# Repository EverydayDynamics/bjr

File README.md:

# bjr
A Ball Juggling Robot's repository

## Getting started

### firmware build and flashing

install rust on you computer
```
curl --proto '=https' --tlsv1.2 -sSf https://sh.rustup.rs | sh
```
Install the target toolchain

```
rustup target add thumbv7em-none-eabihf
```

Install probe-rs
```
curl --proto '=https' --tlsv1.2 -LsSf https://github.com/probe-rs/probe-rs/releases/latest/download/probe-rs-tools-installer.sh | sh
```
Download and install jlink tools from here
https://www.segger.com/downloads/jlink/
Restart your shell
Change directory to the main software
```
cd software/central_control_firmware
```

Build the firmware with:
```
cargo embed --bin main_app --release 
```
### telemetry visualizer build
Change directory to the visualizer
```
cd software/telemetry_visualizer
```

Build the visualizer with:
```
cargo embed --bin main_app --release 
```

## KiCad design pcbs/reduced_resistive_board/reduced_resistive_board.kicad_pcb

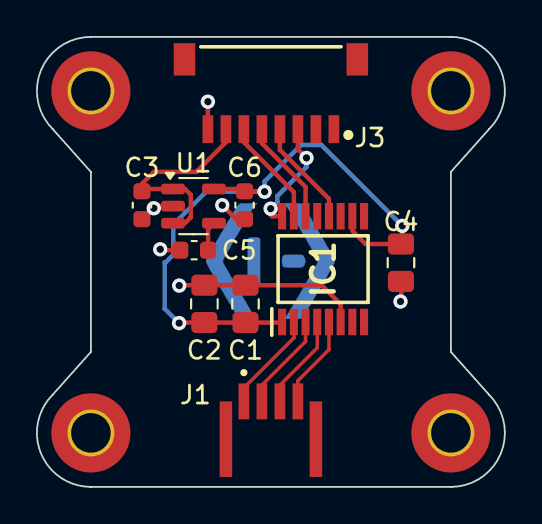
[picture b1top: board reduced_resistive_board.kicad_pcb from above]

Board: 2 copper layers, 26.0 x 25.0 mm, 10 parts (0 on the bottom side), 12 nets.

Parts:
C1, C4: 0.1uF; C_0805_2012Metric_Pad1.18x1.45mm_HandSolder
C2: 10uF; C_0805_2012Metric_Pad1.18x1.45mm_HandSolder
C3, C6: 1uF; C_0603_1608Metric
C5: 0.1uF; C_0603_1608Metric
IC1: TSC2046EIPWR; SOP65P640X120-16N
J1: SFW4R-1STE1HLF; AMPHENOL_SFW4R-1STE1HLF
J3: SM08B-SRSS-TB_LF__SN_; JST_SM08B-SRSS-TB_LF__SN_
U1: SOT-23-5

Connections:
+2V8: C1.1, C2.1, C4.1, C6.1, IC1.1 (+VCC), IC1.10 (IOVDD), U1.5 (V_O)
/CS_TOUCH: IC1.15 (~CS), J3.6
/MISO: IC1.12 (DOUT), J3.4
/MOSI: IC1.14 (DIN), J3.5
/SCK: IC1.16 (DCLK), J3.3
/X+: IC1.2 (X+), J1.1
/X-: IC1.4 (X-), J1.3
/Y+: IC1.3 (Y+), J1.2
/Y-: IC1.5 (Y-), J1.4
GND: C1.2, C2.2, C3.2, C4.2, C5.2, C6.2, IC1.6 (GND), J3.8, U1.2 (GND)
unnamed: C5.1, U1.4 (BYPASS)
VDD: C3.1, J3.7, U1.1 (V_I), U1.3 (V_INH)

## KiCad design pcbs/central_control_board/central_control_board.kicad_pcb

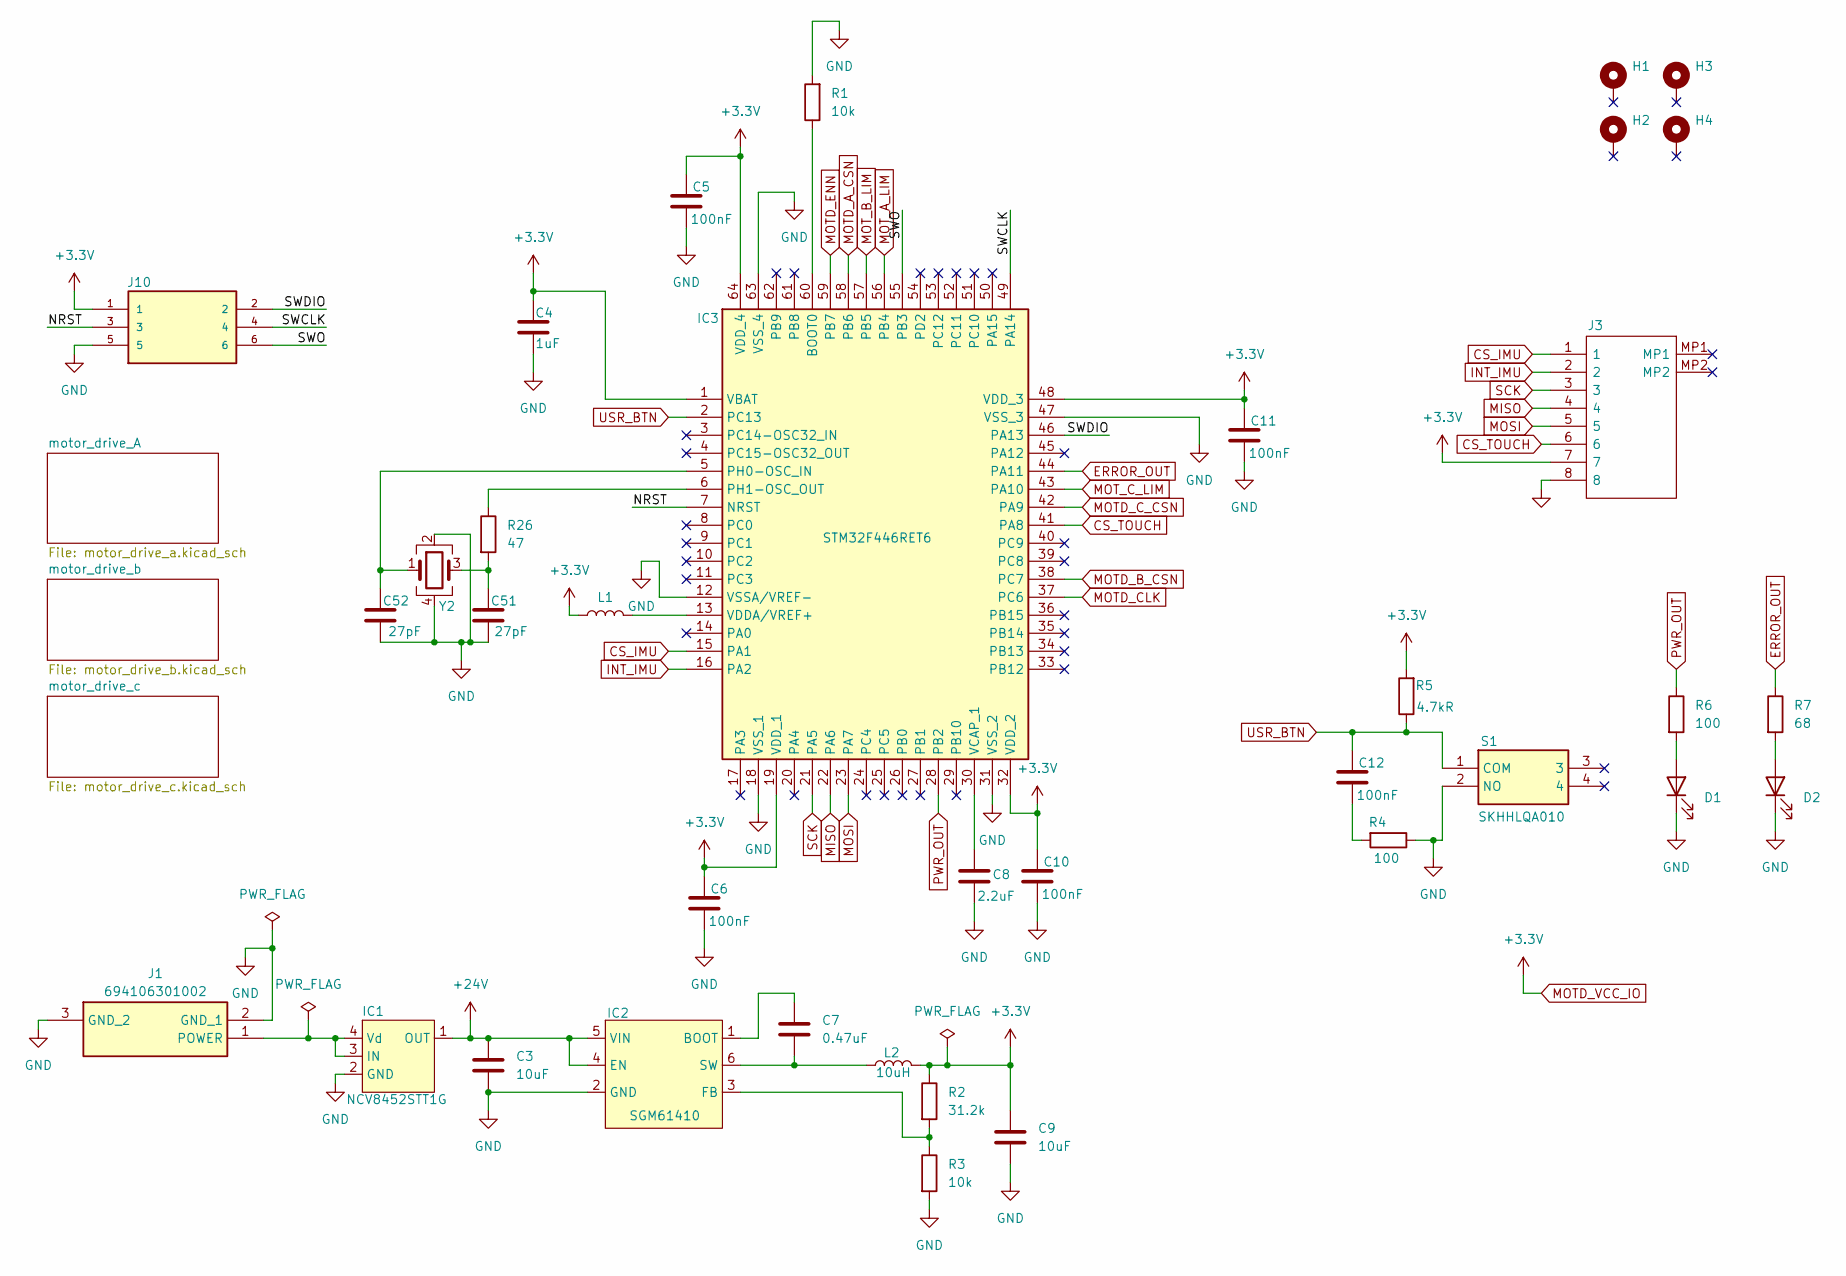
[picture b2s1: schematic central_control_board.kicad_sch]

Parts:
C3, C9: 10uF; C_1206_3216Metric_Pad1.33x1.80mm_HandSolder
C4: 1uF; C_0603_1608Metric_Pad1.08x0.95mm_HandSolder
C5, C6, C10, C11, C12: 100nF; C_0603_1608Metric_Pad1.08x0.95mm_HandSolder
C7: 0.47uF; C_0603_1608Metric_Pad1.08x0.95mm_HandSolder
C8: 2.2uF; C_0603_1608Metric_Pad1.08x0.95mm_HandSolder
C51, C52: 27pF; C_0603_1608Metric_Pad1.08x0.95mm_HandSolder
D1: LED red; LED_0603_1608Metric_Pad1.05x0.95mm_HandSolder
D2: LED white; LED_0603_1608Metric_Pad1.05x0.95mm_HandSolder
H1, H2, H3, H4: MountingHole_Pad; MountingHole_2.7mm_M2.5_ISO14580_Pad
IC1: NCV8452STT1G; SOT-223
IC2: SGM61410; SOT-23-6; mfg_part_num SGM61410XN6G/TR
IC3: STM32F446RET6; LQFP64-10x10mm; Manufacturer_Part_Number STM32F446RET6
J1: 694106301002; Manufacturer_Part_Number 694106301002
J3: BM08B-SRSS-TBT_LF__SN_; BM08BSRSSTBTLFSN; Manufacturer_Part_Number BM08B-SRSS-TBT(LF)(SN)
J10: 8.06.16_J-LINK_6-PIN_NEEDLE_ADAPTER; SEGGER_8.06.16_J-LINK_6-PIN_NEEDLE_ADAPTER; PARTREV A
L1: bead; L_1206_3216Metric
L2: 10uH; LQH3NPN100MJRL
R1, R3: 10k; R_0603_1608Metric_Pad0.98x0.95mm_HandSolder
R2: 31.2k; R_0603_1608Metric_Pad0.98x0.95mm_HandSolder
R4, R6: 100; R_0603_1608Metric_Pad0.98x0.95mm_HandSolder
R5: 4.7kR; R_0603_1608Metric_Pad0.98x0.95mm_HandSolder
R7: 68; R_0603_1608Metric_Pad0.98x0.95mm_HandSolder
R26: 47; R_0603_1608Metric_Pad0.98x0.95mm_HandSolder
S1: SKHHLQA010
Y2: Crystal_GND24; Crystal_SMD_5032-4Pin_5.0x3.2mm

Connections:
+24V: C3.1, IC1.1 (OUT), IC2.4 (EN), IC2.5 (VIN); also elsewhere on the board
/NRST: IC3.7 (NRST), J10.3
/SWCLK: IC3.49 (PA14), J10.4
/SWDIO: IC3.46 (PA13), J10.2
/SWO: IC3.55 (PB3), J10.6
CS_IMU: IC3.15 (PA1), J3.1
CS_TOUCH: IC3.41 (PA8), J3.6
ERROR_OUT: IC3.44 (PA11), R7.1
GND: C3.2, C4.1, C5.2, C6.2, C8.1, C9.2, C10.2, C11.2, C51.2, C52.2, D1.1 (K), D2.1 (K), IC1.2 (GND), IC2.2 (GND), IC3.12 (VSSA/VREF-), IC3.18 (VSS_1), IC3.31 (VSS_2), IC3.47 (VSS_3), IC3.63 (VSS_4), J1.2 (GND_1), J1.3 (GND_2), J3.8, J10.5, R1.2, R3.2, R4.1, S1.2 (NO), Y2.2, Y2.4; also elsewhere on the board
INT_IMU: IC3.16 (PA2), J3.2
MISO: IC3.22 (PA6), J3.4; also elsewhere on the board
MOSI: IC3.23 (PA7), J3.5; also elsewhere on the board
MOTD_A_CSN: IC3.58 (PB6); also elsewhere on the board
MOTD_B_CSN: IC3.38 (PC7); also elsewhere on the board
MOTD_CLK: IC3.37 (PC6); also elsewhere on the board
MOTD_C_CSN: IC3.42 (PA9); also elsewhere on the board
MOTD_ENN: IC3.59 (PB7); also elsewhere on the board
MOTD_VCC_IO: C4.2, C5.1, C6.1, C9.1, C10.1, C11.1, IC3.1 (VBAT), IC3.19 (VDD_1), IC3.32 (VDD_2), IC3.48 (VDD_3), IC3.64 (VDD_4), J3.7, J10.1, L1.1, L2.2, R2.1, R5.2; also elsewhere on the board
MOT_A_LIM: IC3.56 (PB4); also elsewhere on the board
MOT_B_LIM: IC3.57 (PB5); also elsewhere on the board
MOT_C_LIM: IC3.43 (PA10); also elsewhere on the board
unnamed: C12.2, R4.2
unnamed: C51.1, R26.2, Y2.3
unnamed: D1.2 (A), R6.2
unnamed: D2.2 (A), R7.2
unnamed: IC1.3 (IN), IC1.4 (Vd), J1.1 (POWER)
unnamed: C7.1, IC2.1 (BOOT)
unnamed: IC2.3 (FB), R2.2, R3.1
unnamed: C7.2, IC2.6 (SW), L2.1
unnamed: IC3.60 (BOOT0), R1.1
unnamed: C52.1, IC3.5 (PH0-OSC_IN), Y2.1
unnamed: IC3.6 (PH1-OSC_OUT), R26.1
unnamed: C8.2, IC3.30 (VCAP_1)
unnamed: IC3.13 (VDDA/VREF+), L1.2
PWR_OUT: IC3.28 (PB2), R6.1
SCK: IC3.21 (PA5), J3.3; also elsewhere on the board
USR_BTN: C12.1, IC3.2 (PC13), R5.1, S1.1 (COM)

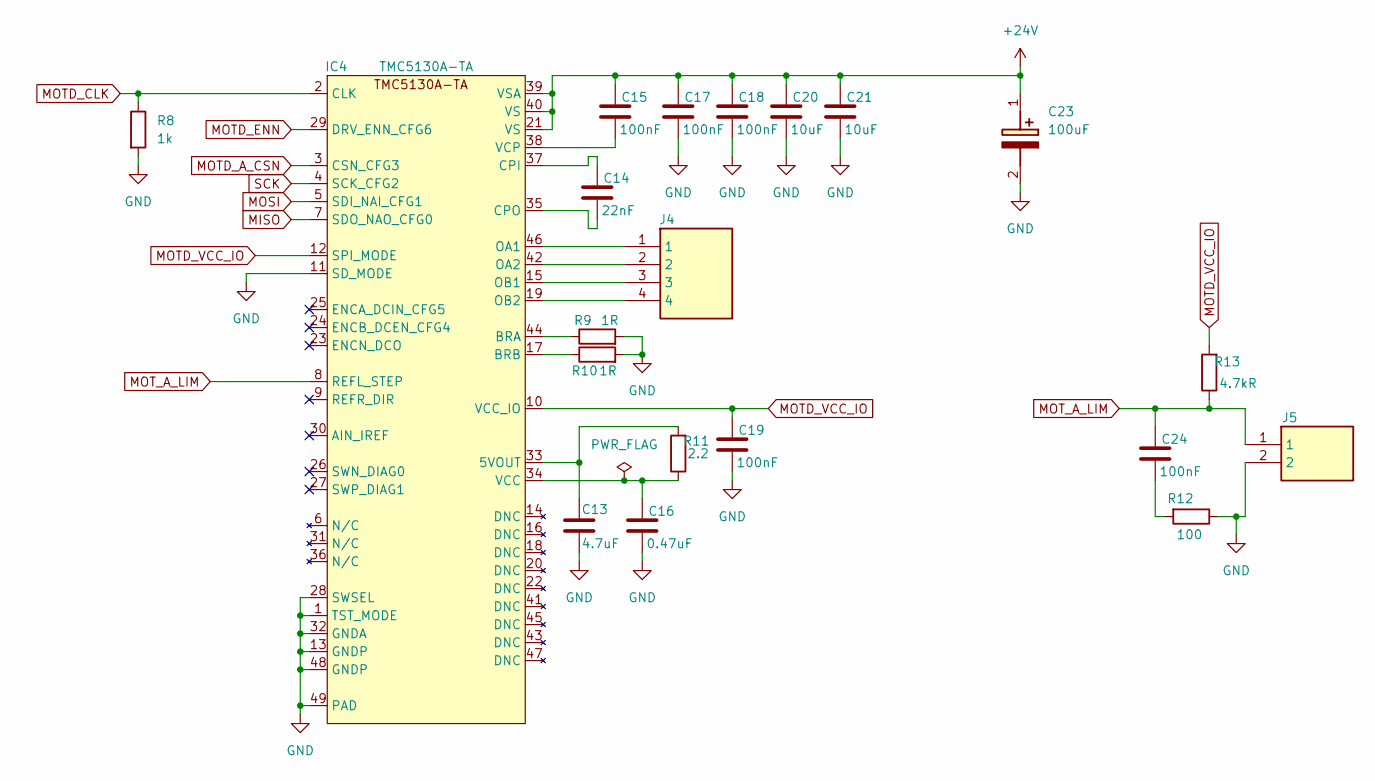
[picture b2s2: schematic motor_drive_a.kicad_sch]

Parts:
C13: 4.7uF; C_0603_1608Metric_Pad1.08x0.95mm_HandSolder
C14: 22nF; C_0603_1608Metric_Pad1.08x0.95mm_HandSolder
C15, C17, C18, C19, C24: 100nF; C_0603_1608Metric_Pad1.08x0.95mm_HandSolder
C16: 0.47uF; C_0603_1608Metric_Pad1.08x0.95mm_HandSolder
C20, C21: 10uF; C_1206_3216Metric_Pad1.33x1.80mm_HandSolder
C23: 100uF; CAPPRD250W50D655H1250
IC4: TMC5130A-TA; TQFP-48-1EP_7x7mm_P0.5mm_EP5x5mm_ThermalVias
J4: B4B-ZR_LF__SN_; SHDR4W50P0X150_1X4_750X350X450P; Manufacturer_Part_Number B4B-ZR(LF)(SN)
J5: B2B-ZR_LF__SN_; SHDR2W50P0X150_1X2_450X350X450P; Manufacturer_Part_Number B2B-ZR(LF)(SN)
R8: 1k; R_0603_1608Metric_Pad0.98x0.95mm_HandSolder
R9, R10: 1R; R_1206_3216Metric_Pad1.30x1.75mm_HandSolder
R11: 2.2; R_0603_1608Metric_Pad0.98x0.95mm_HandSolder
R12: 100; R_0603_1608Metric_Pad0.98x0.95mm_HandSolder
R13: 4.7kR; R_0603_1608Metric_Pad0.98x0.95mm_HandSolder

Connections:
+24V: C15.1, C17.1, C18.1, C20.1, C21.1, C23.1 (+), IC4.21 (VS), IC4.39 (VSA), IC4.40 (VS); also elsewhere on the board
GND: C13.2, C16.2, C17.2, C18.2, C19.2, C20.2, C21.2, C23.2 (-), IC4.1 (TST_MODE), IC4.11 (SD_MODE), IC4.13 (GNDP), IC4.28 (SWSEL), IC4.32 (GNDA), IC4.48 (GNDP), IC4.49 (PAD), J5.2, R8.2, R9.2, R10.2, R12.1; also elsewhere on the board
MISO: IC4.7 (SDO_NAO_CFG0); also elsewhere on the board
MOSI: IC4.5 (SDI_NAI_CFG1); also elsewhere on the board
MOTD_A_CSN: IC4.3 (CSN_CFG3); also elsewhere on the board
MOTD_CLK: IC4.2 (CLK), R8.1; also elsewhere on the board
MOTD_ENN: IC4.29 (DRV_ENN_CFG6); also elsewhere on the board
MOTD_VCC_IO: C19.1, IC4.10 (VCC_IO), IC4.12 (SPI_MODE), R13.2; also elsewhere on the board
MOT_A_LIM: C24.1, IC4.8 (REFL_STEP), J5.1, R13.1; also elsewhere on the board
unnamed: C24.2, R12.2
unnamed: C13.1, IC4.33 (5VOUT), R11.2
unnamed: IC4.44 (BRA), R9.1
unnamed: IC4.17 (BRB), R10.1
unnamed: C14.1, IC4.37 (CPI)
unnamed: C14.2, IC4.35 (CPO)
unnamed: IC4.46 (OA1), J4.1
unnamed: IC4.42 (OA2), J4.2
unnamed: IC4.15 (OB1), J4.3
unnamed: IC4.19 (OB2), J4.4
unnamed: C16.1, IC4.34 (VCC), R11.1
unnamed: C15.2, IC4.38 (VCP)
SCK: IC4.4 (SCK_CFG2); also elsewhere on the board

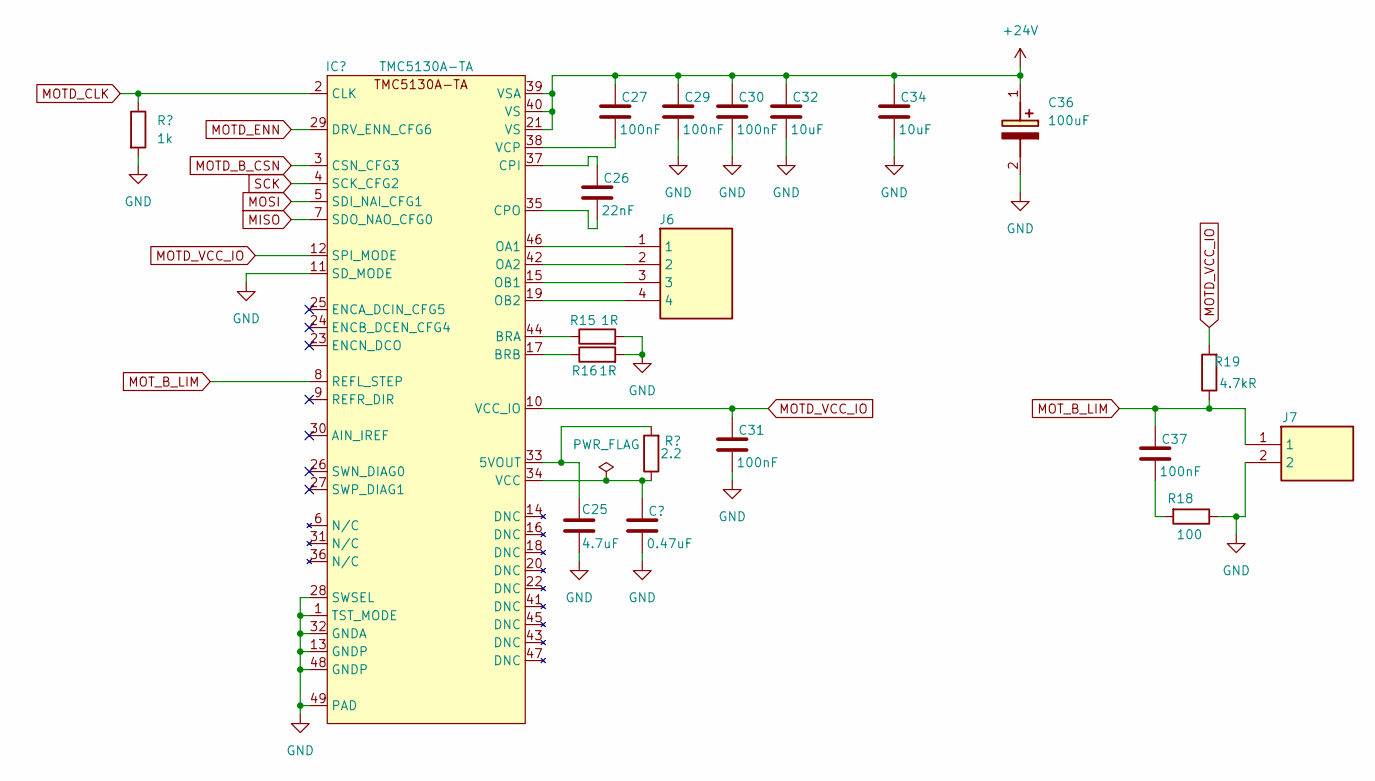
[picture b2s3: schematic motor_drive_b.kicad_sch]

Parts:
C25: 4.7uF; C_0603_1608Metric_Pad1.08x0.95mm_HandSolder
C26: 22nF; C_0603_1608Metric_Pad1.08x0.95mm_HandSolder
C27, C29, C30, C31, C37: 100nF; C_0603_1608Metric_Pad1.08x0.95mm_HandSolder
C28: 0.47uF; C_0603_1608Metric_Pad1.08x0.95mm_HandSolder
C32, C34: 10uF; C_1206_3216Metric_Pad1.33x1.80mm_HandSolder
C36: 100uF; CAPPRD250W50D655H1250
IC5: TMC5130A-TA; TQFP-48-1EP_7x7mm_P0.5mm_EP5x5mm_ThermalVias
J6: B4B-ZR_LF__SN_; SHDR4W50P0X150_1X4_750X350X450P; Manufacturer_Part_Number B4B-ZR(LF)(SN)
J7: B2B-ZR_LF__SN_; SHDR2W50P0X150_1X2_450X350X450P; Manufacturer_Part_Number B2B-ZR(LF)(SN)
R14: 1k; R_0603_1608Metric_Pad0.98x0.95mm_HandSolder
R15, R16: 1R; R_1206_3216Metric_Pad1.30x1.75mm_HandSolder
R17: 2.2; R_0603_1608Metric_Pad0.98x0.95mm_HandSolder
R18: 100; R_0603_1608Metric_Pad0.98x0.95mm_HandSolder
R19: 4.7kR; R_0603_1608Metric_Pad0.98x0.95mm_HandSolder

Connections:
+24V: C27.1, C29.1, C30.1, C32.1, C34.1, C36.1 (+), IC5.21 (VS), IC5.39 (VSA), IC5.40 (VS); also elsewhere on the board
GND: C25.2, C28.2, C29.2, C30.2, C31.2, C32.2, C34.2, C36.2 (-), IC5.1 (TST_MODE), IC5.11 (SD_MODE), IC5.13 (GNDP), IC5.28 (SWSEL), IC5.32 (GNDA), IC5.48 (GNDP), IC5.49 (PAD), J7.2, R14.2, R15.2, R16.2, R18.1; also elsewhere on the board
MISO: IC5.7 (SDO_NAO_CFG0); also elsewhere on the board
MOSI: IC5.5 (SDI_NAI_CFG1); also elsewhere on the board
MOTD_B_CSN: IC5.3 (CSN_CFG3); also elsewhere on the board
MOTD_CLK: IC5.2 (CLK), R14.1; also elsewhere on the board
MOTD_ENN: IC5.29 (DRV_ENN_CFG6); also elsewhere on the board
MOTD_VCC_IO: C31.1, IC5.10 (VCC_IO), IC5.12 (SPI_MODE), R19.2; also elsewhere on the board
MOT_B_LIM: C37.1, IC5.8 (REFL_STEP), J7.1, R19.1; also elsewhere on the board
unnamed: C37.2, R18.2
unnamed: C25.1, IC5.33 (5VOUT), R17.2
unnamed: IC5.44 (BRA), R15.1
unnamed: IC5.17 (BRB), R16.1
unnamed: C26.1, IC5.37 (CPI)
unnamed: C26.2, IC5.35 (CPO)
unnamed: IC5.46 (OA1), J6.1
unnamed: IC5.42 (OA2), J6.2
unnamed: IC5.15 (OB1), J6.3
unnamed: IC5.19 (OB2), J6.4
unnamed: C28.1, IC5.34 (VCC), R17.1
unnamed: C27.2, IC5.38 (VCP)
SCK: IC5.4 (SCK_CFG2); also elsewhere on the board

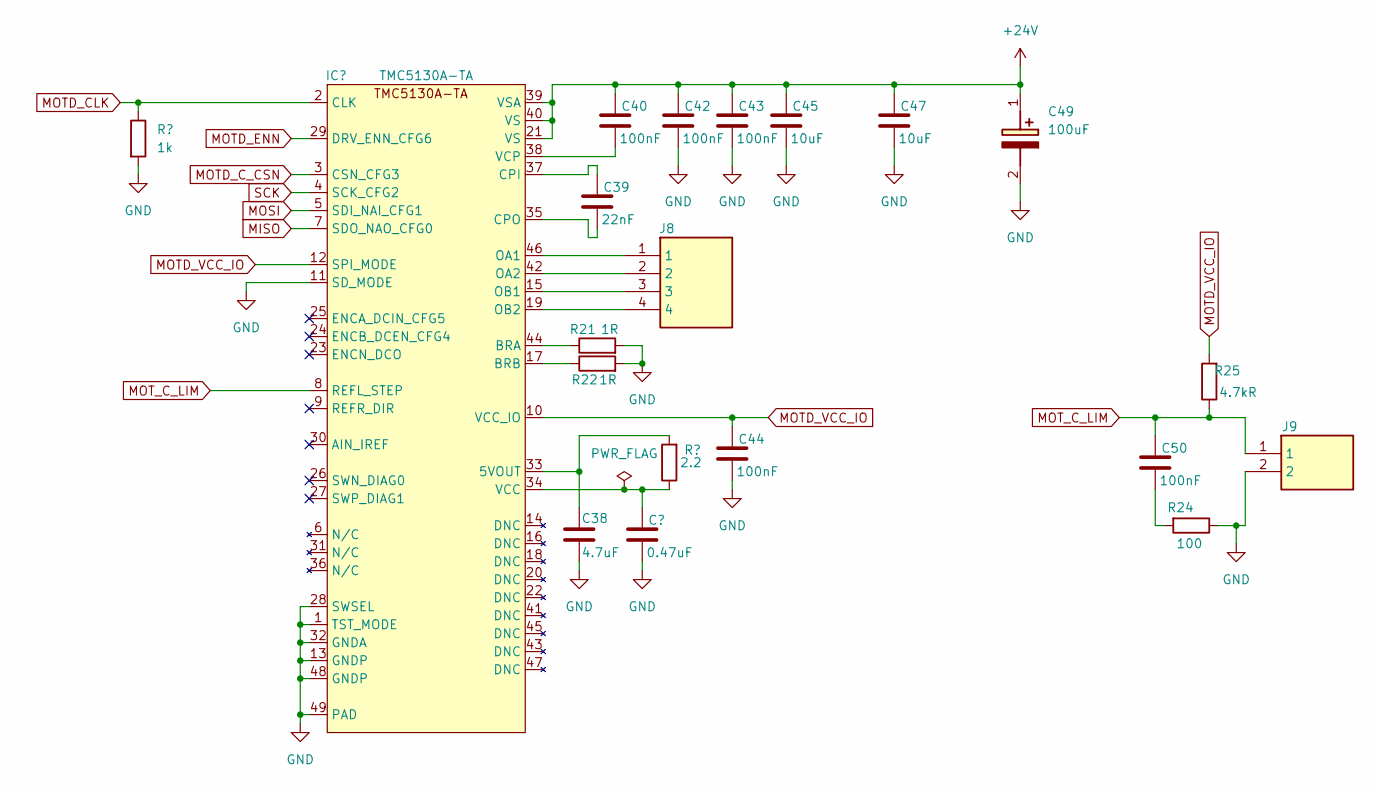
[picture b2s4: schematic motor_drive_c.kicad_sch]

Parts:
C38: 4.7uF; C_0603_1608Metric_Pad1.08x0.95mm_HandSolder
C39: 22nF; C_0603_1608Metric_Pad1.08x0.95mm_HandSolder
C40, C42, C43, C44, C50: 100nF; C_0603_1608Metric_Pad1.08x0.95mm_HandSolder
C41: 0.47uF; C_0603_1608Metric_Pad1.08x0.95mm_HandSolder
C45, C47: 10uF; C_1206_3216Metric_Pad1.33x1.80mm_HandSolder
C49: 100uF; CAPPRD250W50D655H1250
IC6: TMC5130A-TA; TQFP-48-1EP_7x7mm_P0.5mm_EP5x5mm_ThermalVias
J8: B4B-ZR_LF__SN_; SHDR4W50P0X150_1X4_750X350X450P; Manufacturer_Part_Number B4B-ZR(LF)(SN)
J9: B2B-ZR_LF__SN_; SHDR2W50P0X150_1X2_450X350X450P; Manufacturer_Part_Number B2B-ZR(LF)(SN)
R20: 1k; R_0603_1608Metric_Pad0.98x0.95mm_HandSolder
R21, R22: 1R; R_1206_3216Metric_Pad1.30x1.75mm_HandSolder
R23: 2.2; R_0603_1608Metric_Pad0.98x0.95mm_HandSolder
R24: 100; R_0603_1608Metric_Pad0.98x0.95mm_HandSolder
R25: 4.7kR; R_0603_1608Metric_Pad0.98x0.95mm_HandSolder

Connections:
+24V: C40.1, C42.1, C43.1, C45.1, C47.1, C49.1 (+), IC6.21 (VS), IC6.39 (VSA), IC6.40 (VS); also elsewhere on the board
GND: C38.2, C41.2, C42.2, C43.2, C44.2, C45.2, C47.2, C49.2 (-), IC6.1 (TST_MODE), IC6.11 (SD_MODE), IC6.13 (GNDP), IC6.28 (SWSEL), IC6.32 (GNDA), IC6.48 (GNDP), IC6.49 (PAD), J9.2, R20.2, R21.2, R22.2, R24.1; also elsewhere on the board
MISO: IC6.7 (SDO_NAO_CFG0); also elsewhere on the board
MOSI: IC6.5 (SDI_NAI_CFG1); also elsewhere on the board
MOTD_CLK: IC6.2 (CLK), R20.1; also elsewhere on the board
MOTD_C_CSN: IC6.3 (CSN_CFG3); also elsewhere on the board
MOTD_ENN: IC6.29 (DRV_ENN_CFG6); also elsewhere on the board
MOTD_VCC_IO: C44.1, IC6.10 (VCC_IO), IC6.12 (SPI_MODE), R25.2; also elsewhere on the board
MOT_C_LIM: C50.1, IC6.8 (REFL_STEP), J9.1, R25.1; also elsewhere on the board
unnamed: C50.2, R24.2
unnamed: C38.1, IC6.33 (5VOUT), R23.2
unnamed: IC6.44 (BRA), R21.1
unnamed: IC6.17 (BRB), R22.1
unnamed: C39.1, IC6.37 (CPI)
unnamed: C39.2, IC6.35 (CPO)
unnamed: IC6.46 (OA1), J8.1
unnamed: IC6.42 (OA2), J8.2
unnamed: IC6.15 (OB1), J8.3
unnamed: IC6.19 (OB2), J8.4
unnamed: C41.1, IC6.34 (VCC), R23.1
unnamed: C40.2, IC6.38 (VCP)
SCK: IC6.4 (SCK_CFG2); also elsewhere on the board

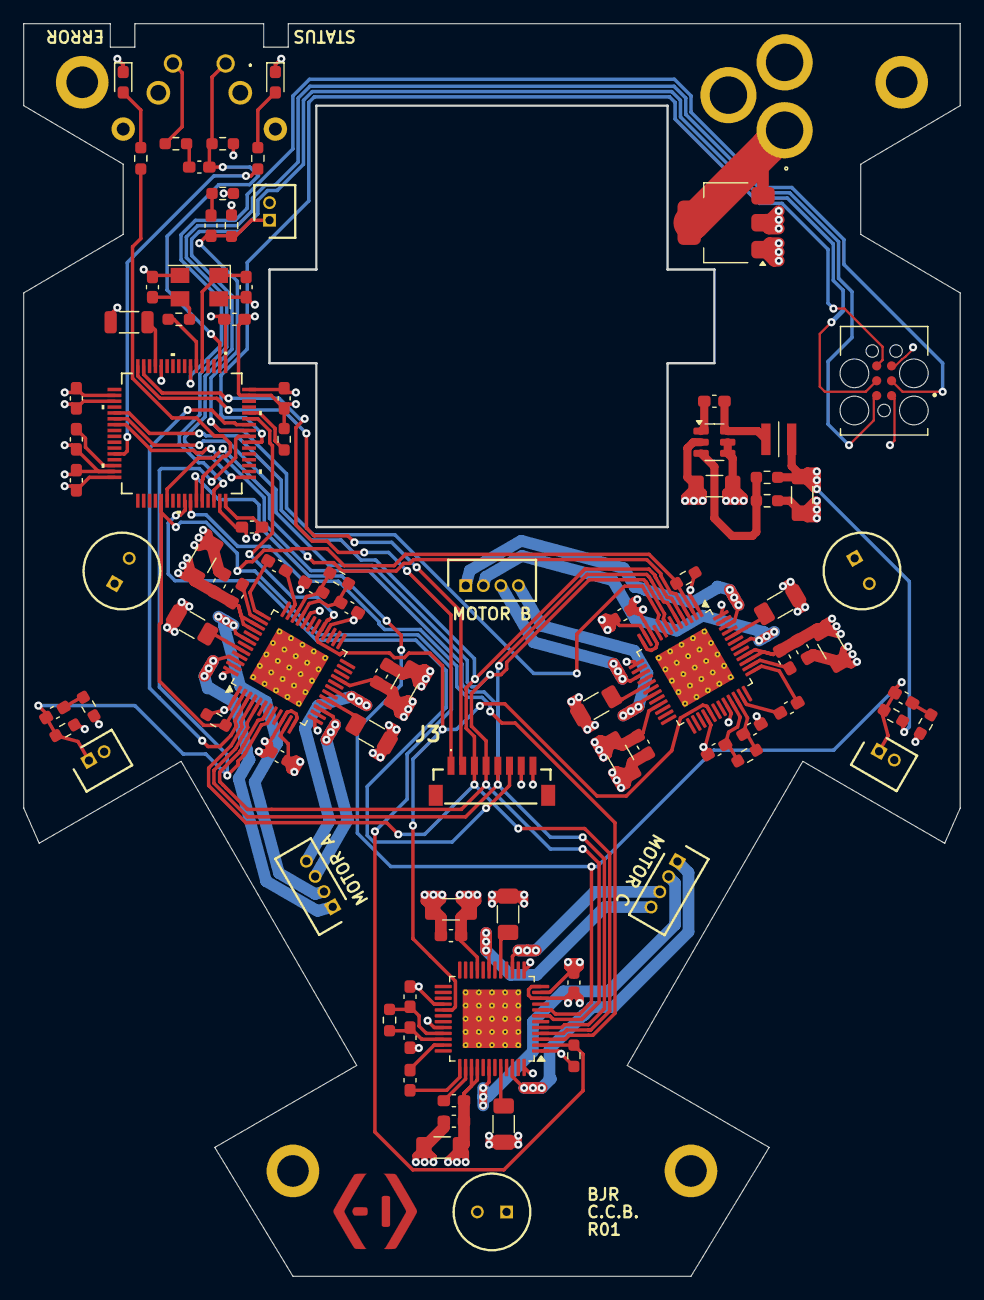
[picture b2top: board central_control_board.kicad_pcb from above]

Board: 4 copper layers, 80.0 x 107.0 mm, 96 parts (0 on the bottom side), 73 nets.

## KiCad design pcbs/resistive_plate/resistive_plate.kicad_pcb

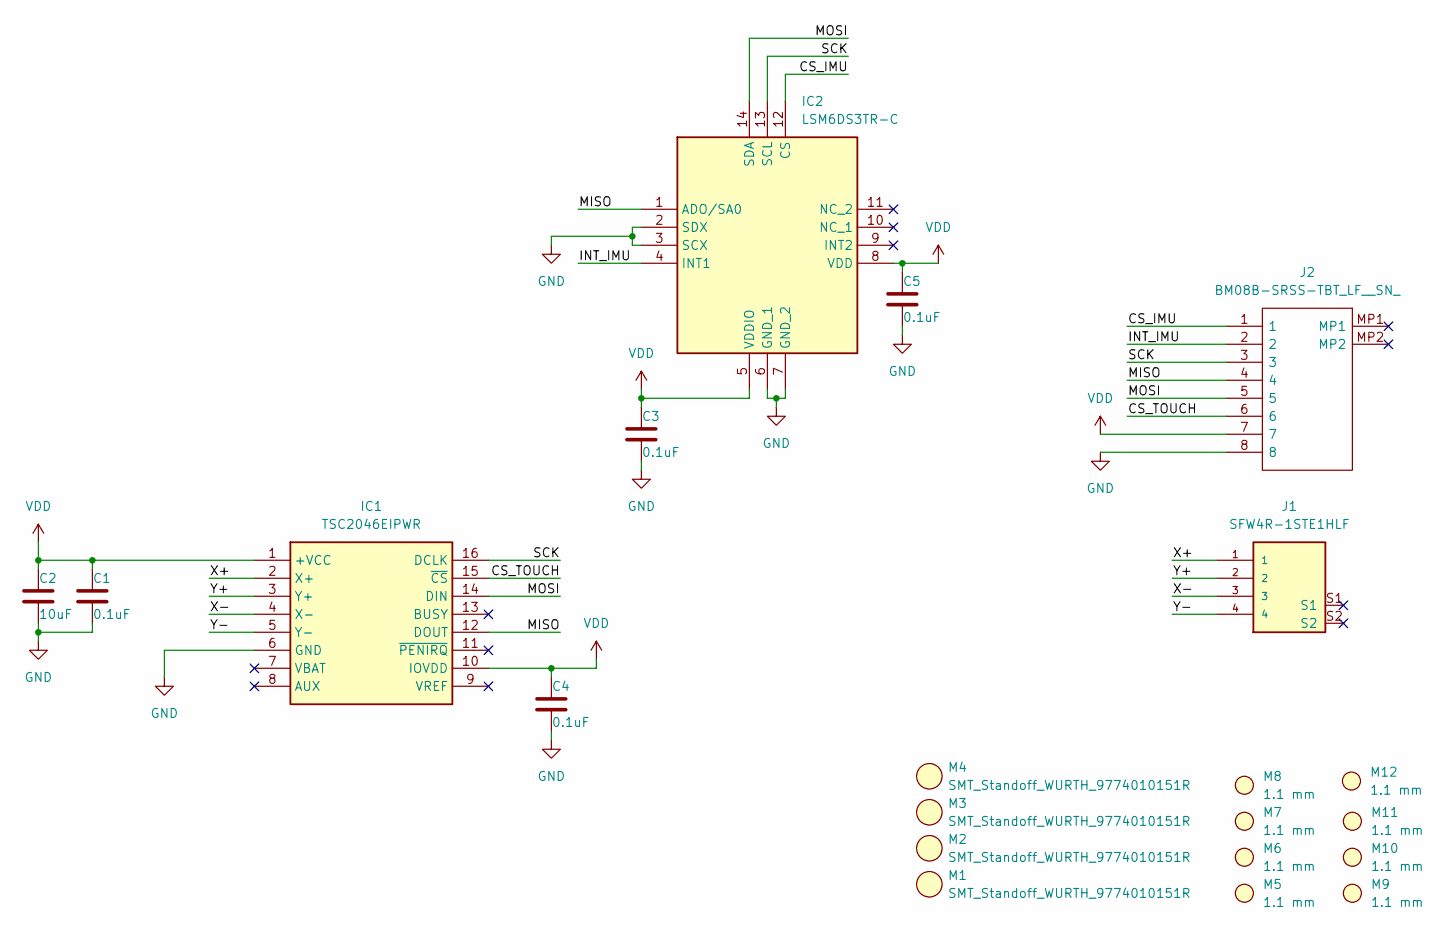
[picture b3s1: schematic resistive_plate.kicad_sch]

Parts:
C1, C3, C4, C5: 0.1uF; C_0805_2012Metric_Pad1.18x1.45mm_HandSolder
C2: 10uF; C_0805_2012Metric_Pad1.18x1.45mm_HandSolder
IC1: TSC2046EIPWR; SOP65P640X120-16N; Mouser Part Number 595-TSC2046EIPWR
IC2: LSM6DS3TR-C; LGA-14_2.5X3X0.86_; Mouser Part Number 511-LSM6DS3TR-C
J1: SFW4R-1STE1HLF; AMPHENOL_SFW4R-1STE1HLF; PARTREV B
J2: BM08B-SRSS-TBT_LF__SN_; BM08BSRSSTBTLFSN; Manufacturer_Part_Number BM08B-SRSS-TBT(LF)(SN)
M1, M2, M3, M4: WURTH ELEKTRONIK 9774010151R
M5, M6, M7, M8, M9, M10, M11, M12: 1.1 mm; Mounting hole 1.1 mm

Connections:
/CS_IMU: IC2.12 (CS), J2.1
/CS_TOUCH: IC1.15 (~CS), J2.6
/INT_IMU: IC2.4 (INT1), J2.2
/MISO: IC1.12 (DOUT), IC2.1 (ADO/SA0), J2.4
/MOSI: IC1.14 (DIN), IC2.14 (SDA), J2.5
/SCK: IC1.16 (DCLK), IC2.13 (SCL), J2.3
/X+: IC1.2 (X+), J1.1
/X-: IC1.4 (X-), J1.3
/Y+: IC1.3 (Y+), J1.2
/Y-: IC1.5 (Y-), J1.4
GND: C1.2, C2.2, C3.2, C4.2, C5.2, IC1.6 (GND), IC2.2 (SDX), IC2.3 (SCX), IC2.6 (GND_1), IC2.7 (GND_2), J2.8
VDD: C1.1, C2.1, C3.1, C4.1, C5.1, IC1.1 (+VCC), IC1.10 (IOVDD), IC2.5 (VDDIO), IC2.8 (VDD), J2.7

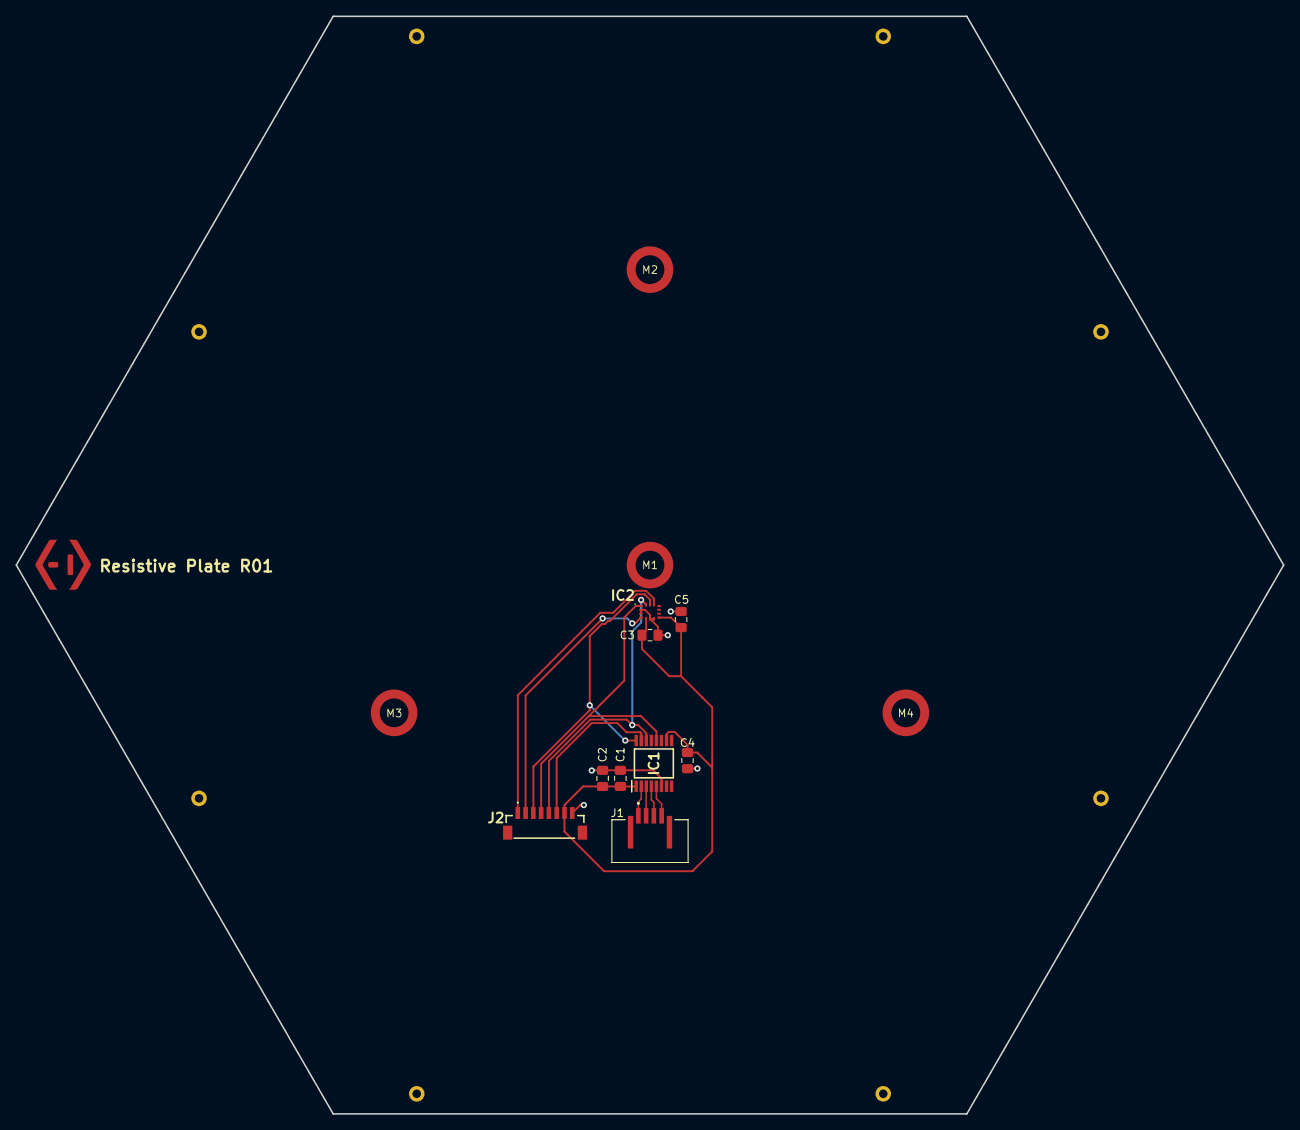
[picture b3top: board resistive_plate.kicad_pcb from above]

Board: 2 copper layers, 163.0 x 141.2 mm, 21 parts (0 on the bottom side), 12 nets.

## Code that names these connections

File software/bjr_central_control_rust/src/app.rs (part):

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    use core::sync::atomic::Ordering;
    use stm32f4xx_hal::{timer::{CounterUs, Event},
                        gpio::{gpioa::PA0,
                               gpioa::PA5,
                               gpioa::PA1,
                               gpioa::PA4,
                               gpioa::PA6,
                               gpioa::PA7,
                               gpioa::PA8,
                               gpioa::PA9,
                               gpiob::PB4,
                               gpiob::PB5,
                               gpiob::PB6,
                               Output, Input},
                        i2c::I2c,
                        pac::I2C1,
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    const SYSFREQ: u32 = 150_000_000;
    static STEPPERS_STATE: [StepperState;NUM_ACTUATOR] = [StepperState::new(),StepperState::new(),StepperState::new()];
    type MotorLiteral= MotorEnum<
        LinearStepperMotor<'static, Lga201s06AUecb019, SilentStepStick<PB4<Input>>>,
        LinearStepperMotor<'static, Lga201s06AUecb019, SilentStepStick<PB5<Input>>>,
        LinearStepperMotor<'static, Lga201s06AUecb019, SilentStepStick<PB6<Input>>>
    >;
    // Shared resources go here
    #[shared]
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        i2c: Option<I2c<I2C1>>,
        controller_task: ControllerTask,
        initializer_task: Initializer,
        stepper_task_a: StepperCtrlrTask<'static, PA5<Output>,PA0<Output>>,
        stepper_task_b: StepperCtrlrTask<'static, PA6<Output>,PA7<Output>>,
        stepper_task_c: StepperCtrlrTask<'static, PA8<Output>,PA9<Output>>,
        stepper_main_timer: CounterUs<stm32f4xx_hal::pac::TIM2>,
        time: u64,
        debug_pin: PA1<Output>,
        debug_pin2: PA4<Output>,
    }
    #[monotonic(binds = TIM3, default = true)]
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        let gpiob = ctx.device.GPIOB.split();
        // button
        // led
        let stepper_a_stp_pin = gpioa.pa5.into_push_pull_output();
        let stepper_a_dir_pin = gpioa.pa0.into_push_pull_output();
        let stepper_a_diag_pin = gpiob.pb4.into_pull_down_input();

        let stepper_b_stp_pin = gpioa.pa6.into_push_pull_output();
        let stepper_b_dir_pin = gpioa.pa7.into_push_pull_output();
        let stepper_b_diag_pin = gpiob.pb5.into_pull_down_input();

        let stepper_c_stp_pin = gpioa.pa8.into_push_pull_output();
        let stepper_c_dir_pin = gpioa.pa9.into_push_pull_output();
        let stepper_c_diag_pin = gpiob.pb6.into_pull_down_input();

        let mut debug_pin = gpioa.pa1.into_push_pull_output();
        let mut debug_pin2 = gpioa.pa4.into_push_pull_output();

        let (stp_setp_a_prod, stp_setp_a_cons) = ctx.local.qa.split();
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
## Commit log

2023-11-02 schematics almost ready for plate
2023-11-07 almost done layout
2023-11-13 R01 plate pcb
2023-11-13 Initial software commit, debugging works
2023-11-20 almost there with unit testing
2023-11-20 steppper control works
2023-11-27 whoops, I didn't commit for days
2023-11-29 smoother stepping
2023-11-30 optimized build, about to run fix
2023-12-03 stepper visually good
2023-12-03 inverse kinematics works
2023-12-04 crude homing done
2023-12-17 backup
2024-02-07 inductive test
2024-02-09 inductive test pcb manufactured
2024-02-11 polygon based spiral maker
2024-03-07 adjusting the app remove the need for the gyro
2024-04-23 defmt tester copied over
2024-04-24 app building
2024-04-26 working bulk action
2024-05-17 stage tsc tests
2024-06-03 tsc2046 test
2024-07-15 stage file
2024-07-16 feedforward done
2024-07-19 pretty shitty state
2024-07-19 bjr_bsp created
2024-07-21 wip stepper_driver
2024-07-22 get state implemented
2024-07-22 motor drive works
2024-07-22 bit more shenannies on spistatus
2024-07-23 lil commit before clippy
2024-07-24 limits added
2024-07-24 Clean up motor handler
2024-07-26 big ass changes
2024-07-27 Testing going gooood
2024-07-28 full thing builds
2024-07-29 board support fixed
2024-07-31 Working platform with monotonics
2024-08-01 separate fallible resource taking
2024-08-01 rigged in the state machine
2024-08-02 builder and host runner added, halfway refactoring
2024-08-02 Refactor Done
2024-08-02 homing doing the homing (mostly)
2024-08-04 Add remaining stepper devices
2024-08-05 touch sensor added
2024-08-05 rudimentary touch handler added
2024-08-06 Back to Embedded time, tests fixed
2024-08-06 Tests written for touch handler
2024-08-08 no ball state runner skeleton
2024-08-08 Finished noball tests
2024-08-09 homing and stepping parameters set
2024-08-09 no ball parameter adjustment
2024-08-11 a lot of changes
2024-08-11 Controller Changes
2024-08-11 add inverse kinematics
2024-08-16 first working menu item
2024-08-16 decent menu now
2024-08-16 rtt based running
2024-08-19 finally a stable commit
2024-08-19 little cleanup in bsp
2024-08-19 clippy run
2024-08-19 big refactor
2024-08-19 finally object safe logging
2024-08-23 We've got stable control
2024-08-28 add telemetry
2024-08-29 circling mode add
2024-08-31 mvp bjr sowftware
2024-09-05 renaming bsp_traits to device_traits
2024-09-05 resistive plate pcb R01
2024-09-05 adjustments to spiral generation
2024-09-05 post mgf commit
2024-11-22 central control board R01 production
2024-12-17 enable fix + test motion
2025-01-17 small change, dunno what it does
2025-02-23 software building tutorial added
2025-02-23 mfg version of reduced resistive board
2025-03-31 warning cleanups 2
    warning cleanups 1
    little more cleanup
2025-05-24 trimming feature add
2025-06-03 add csv export to telemetry visualizer
2025-06-03 STAGING
2025-07-11 update but not sure what
2025-07-12 add Flush buffer button to telemetry
2025-07-12 add Flush buffer button to telemetry (#6)
2025-07-12 add ball 2d plot to telemetry
2025-07-12 add ball 2d plot to telemetry (#7)
2025-07-12 Fix my own mess
2025-07-12 initial attempt
2025-07-16 fix plate behaviour
2025-07-16 fix plate direction
2025-07-16 add poly trajectiory
2025-07-19 The elusive triangle pattern is born
2025-08-12 graphics added
2025-08-16 Final decal designs
2025-08-17 add shutdown sequence
2025-09-06 Remove all traces of defmt
2025-09-13 rename packages
2025-09-27 tiny fix
